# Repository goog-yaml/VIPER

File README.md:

# What is VIPR?

Simply put, VIPR is a open source radio node designed and built around North American mesh communication over LoRa built off of an ESP32-S3 platform. Put less simply, VIPR is another ESP32 development board focused more on frontend, hardware, and size. The project aims to create a small, pocketable radio node that can run independently. Currently the procsessing power of it's latest version (2.0) can only handle small workloads and can only run a Real Time OS in comparison to a fully fledged computer.

**VIPR is currently in Alpha testing, soon to be beta!**

## Current Revision

Currently the board packs a 19mm wide footprint without a screen. The end is equipped with an SMA conector for easy antenna swaps and the side boasts an onboard PCB wifi antenna tied to the ESP32-MINI-1 module.

Future revisions intend to add a screen and interactives to the board to further refine the frontend, all that is needed after that is software and a case!

### Changelog

```
* Redid a proper BOM
    * This included sizing and components selection
* Added back the CH340X
* Reverted to old "pen" form factor
* Created a new "lopsided" board end 
* Added a screen header
* Fixed a regulator issue on the radio portion
* bundled CAD files into production folders <=2.1
```

## Docs

Docs will be coming soon!
<br>

## Versioning system

The project follows a versioning system of major and minor. The first number in the version is the board platform. Whenever the board is fully redone a new major version will be released. Whenever the board has a small tweak to an existing platform version the second number behind the first will be bumped up by one.

A board version of say, 2.1 would indicate platform version 2 with one tweak of the original version 2.0.

#### Latest Journal as of July 28th

For revision 2.1. I introduced a versioning system of major and minor.
 What's new in 2.1?

Mounting holes for M2 screws on the left side of the board and a header connection for a screen. the schematics now include test points for serial, power, and JTAG soon to be onboard for revision 2.2.

Some issues were included in revision 2 that would prevent stable operation of the radio caused by a faulty connection between the regulator for the SX1262 and the inductor managing it.

That's all.

-Matias

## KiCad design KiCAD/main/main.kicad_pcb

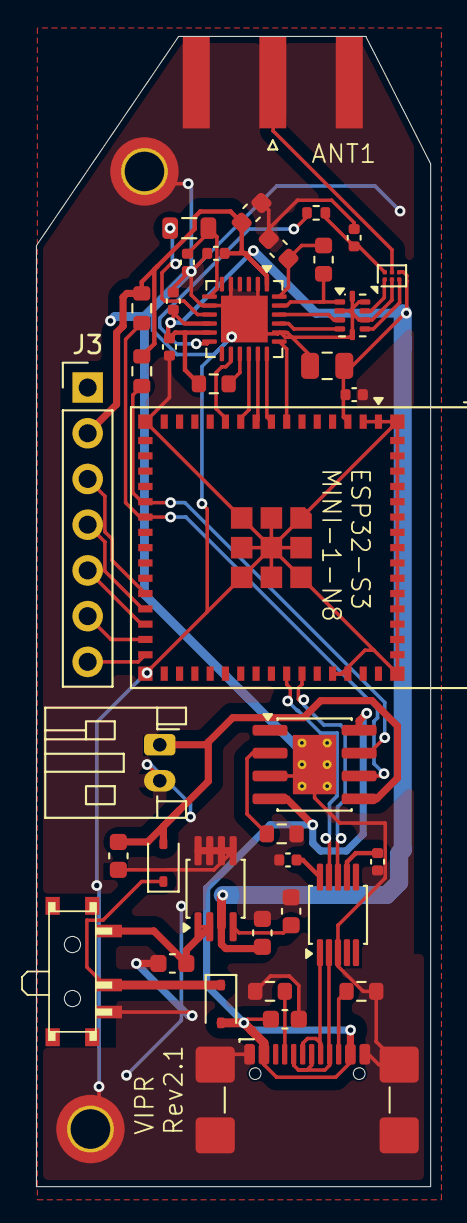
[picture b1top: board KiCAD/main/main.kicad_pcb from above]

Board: 2 copper layers, 21.9 x 63.9 mm, 41 parts (0 on the bottom side), 38 nets.

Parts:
BT1: Battery_Cell; JST_PH_S2B-PH-K_1x02_P2.00mm_Horizontal
C1, C2: 1uF; C_0603_1608Metric
C3: 0.1uf; C_0402_1005Metric
C4: 22uF; C_0805_2012Metric
C5: 470pF; C_0603_1608Metric
C6, C7, C10, C11, C17, C18: 0.1uF; C_0402_1005Metric
C12: 22 pF; C_0603_1608Metric
C13: 100nF; C_0402_1005Metric
C14, C15, C16: 10uF; C_0603_1608Metric
D1, D2: D_Schottky; D_SOD-323
FL1: 0900FM15K0039; Balun_Johanson_0900FM15K0039
H1, H2: MountingHole_Pad; MountingHole_2.2mm_M2_DIN965_Pad_TopBottom
J1: USB_C_Receptacle_USB2.0_14P; USB_C_Receptacle_GCT_USB4110
J2: Conn_Coaxial; SMA_Amphenol_132289_EdgeMount
J3: Conn_01x07_Socket; PinHeader_1x07_P2.54mm_Vertical
L1: 15uH; L_0805_2012Metric
L2: 18 nH; L_0603_1608Metric
R1, R2: 5K1; R_0603_1608Metric
R4, R9, R10: 10K; R_0603_1608Metric
R5: 100R; R_0402_1005Metric
R7: 1.2K; R_0603_1608Metric
SW1: SW_SPDT; SSSS810701
U1: SX1262IMLTRT; QFN-24-1EP_4x4mm_P0.5mm_EP2.6x2.6mm
U2: TP4056-42-ESOP8; SOIC-8-1EP_3.9x4.9mm_P1.27mm_EP2.41x3.3mm_ThermalVias
U3: BGS12P2L; Infineon_PG-TSNP-6-10_0.7x1.1mm_0.7x1.1mm_P0.4mm
U4: ESP32-S3-MINI-1; ESP32-S2-MINI-1
U6: MIC5219-3.3YMM; MSOP-8_3x3mm_P0.65mm
U7: CH340X; MSOP-10_3x3mm_P0.5mm

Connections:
CHRG_BAT: BT1.1 (+), C16.2, D2.2 (A), U2.5 (BAT)
DIO2: R5.1, U1.12 (DIO2)
unnamed: D1.1 (K), D2.1 (K), SW1.2 (B)
unnamed: FL1.3 (RFI_N), U1.22 (RFI_N)
unnamed: FL1.4 (RFI_P), U1.21 (RFI_P)
unnamed: FL1.1 (RFO), L2.2, U1.23 (RFO)
unnamed: FL1.6 (SW_RFI), U3.3 (RF1)
unnamed: FL1.8 (SW_RFO), U3.1 (RF2)
unnamed: J1.A5 (CC1), R1.1
unnamed: J1.B5 (CC2), R2.2
unnamed: J2.1 (In), U3.5 (RFIN)
unnamed: C1.2, SW1.1 (A), U6.1 (EN), U6.2 (IN)
unnamed: L1.2, U1.9 (DCC_SW)
unnamed: C11.2, L1.1, U1.7 (VREG)
unnamed: C12.1, L2.1, U1.24 (VR_PA)
unnamed: R4.2, U1.15 (~RESET)
unnamed: R7.1, U2.2 (PROG)
unnamed: C13.1, R5.2, U3.6 (CTRL)
unnamed: C5.1, U6.4 (BP)
READY: U1.14 (BUSY), U4.11 (IO7)
SCR_CLK: J3.3, U4.26 (IO26)
SCR_CS: J3.7, U4.30 (IO48)
SCR_DC: J3.6, U4.29 (IO34)
SCR_MOSI: J3.4, U4.27 (IO47)
SCR_RES: J3.5, U4.28 (IO33)
SERIAL_N: U4.39 (TXD0), U7.9 (RXD)
SERIAL_P: U4.40 (RXD0), U7.8 (TXD)
SPI_CLK: U1.18 (SCK), U4.8 (IO4)
SPI_CS: U1.19 (NSS), U4.7 (IO3)
SPI_MISO: U1.17 (MOSI), U4.9 (IO5)
SPI_MOSI: U1.16 (MISO), U4.10 (IO6)
USB_DATA+: J1.A6 (D+), J1.B6 (D+), U7.1 (UD+)
USB_DATA-: J1.A7 (D-), J1.B7 (D-), U7.2 (UD-)
V+: C15.1, D1.2 (A), J1.A4 (VBUS), J1.A9 (VBUS), J1.B4 (VBUS), J1.B9 (VBUS), U2.4 (V_{CC}), U2.8 (CE)
V-: BT1.2 (-), C1.1, C2.1, C3.1, C4.1, C5.2, C6.2, C7.2, C10.2, C11.1, C12.2, C13.2, C14.1, C15.2, C16.1, C17.1, C18.1, FL1.2 (GND), FL1.5 (GND), FL1.7 (GND), FL1.9 (GND), FL1.10 (GND), H1.1 (1_1), H2.1 (1_1), J1.A1 (GND), J1.A12 (GND), J1.B1 (GND), J1.B12 (GND), J1.SH (SHIELD), J2.2 (Ext), J3.1, R1.2, R2.1, R7.2, SW1.3 (C), U1.2 (GND), U1.5 (GND), U1.8 (GND), U1.20 (GND), U1.25 (GND), U2.3 (GND), U2.9 (EPAD), U3.2 (GND), U4.1 (GND), U4.2 (GND), U4.42 (GND), U4.43 (GND), U4.46 (GND), U4.47 (GND), U4.48 (GND), U4.49 (GND), U4.50 (GND), U4.51 (GND), U4.52 (GND), U4.53 (GND), U4.54 (GND), U4.55 (GND), U4.56 (GND), U4.57 (GND), U4.58 (GND), U4.59 (GND), U4.60 (GND), U4.61 (GND), U4.62 (GND), U4.63 (GND), U4.64 (GND), U4.65 (GND), U6.5 (GND), U6.6 (GND), U6.7 (GND), U6.8 (GND), U7.3 (GND)
VCC: C2.2, C3.2, C4.2, C6.1, C7.1, C10.1, C14.2, C17.2, C18.2, J3.2, R4.1, R9.2, R10.2, U1.1 (VDD_IN), U1.10 (VBAT), U1.11 (VBAT_IO), U3.4 (VDD), U4.3 (3V3), U6.3 (OUT), U7.7 (VCC), U7.10 (V3)
~CHRG: R10.1, U2.7 (~CHRG), U4.20 (IO16)
~STDBY: R9.1, U2.6 (~STDBY), U4.21 (IO17)

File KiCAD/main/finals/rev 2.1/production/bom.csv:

Designator,Footprint,Quantity,Value,LCSC Part #
BT1,JST_PH_S2B-PH-K_1x02_P2.00mm_Horizontal,1,Battery_Cell,C265094
"C1, C2",0603,2,1uF,C15849
"C10, C11, C17, C18, C3, C6, C7",0402,7,0.1uF,C1525
C12,0603,1,22 pF,C1653
C13,0402,1,100nF,C1525
"C14, C15, C16",0603,3,10uF,C19702
C4,0805,1,22uF,C45783
C5,0603,1,470pF,C1620
"D1, D2",D_SOD-323,2,D_Schottky,C191023
J1,USB_C_Receptacle_GCT_USB4110,1,USB_C_Receptacle_USB2.0_14P,C2765186
J2,SMA_Amphenol_132289_EdgeMount,1,Conn_Coaxial,C3039673
J3,PinHeader_1x07_P2.54mm_Vertical,1,Conn_01x07_Socket,
L1,0805,1,15uH,C383402
L2,0603,1,18 nH,C19721138
"R1, R2",0603,2,5K1,C23186
"R10, R4, R9",0603,3,10K,C25804
R5,0402,1,100R,C25076
R7,0603,1,1.2K,C22765
SW1,SSSS810701,1,SW_SPDT,C97433
U1,QFN-24-1EP_4x4mm_P0.5mm_EP2.6x2.6mm,1,SX1262IMLTRT,C191341
U2,SOIC-8-1EP_3.9x4.9mm_P1.27mm_EP2.41x3.3mm_ThermalVias,1,TP4056-42-ESOP8,C16581
U3,Infineon_PG-TSNP-6-10_0.7x1.1mm_0.7x1.1mm_P0.4mm,1,BGS12P2L,C3312945
U6,MSOP-8_3x3mm_P0.65mm,1,MIC5219-3.3YMM,C628154
U7,MSOP-10_3x3mm_P0.5mm,1,CH340X,C3035748

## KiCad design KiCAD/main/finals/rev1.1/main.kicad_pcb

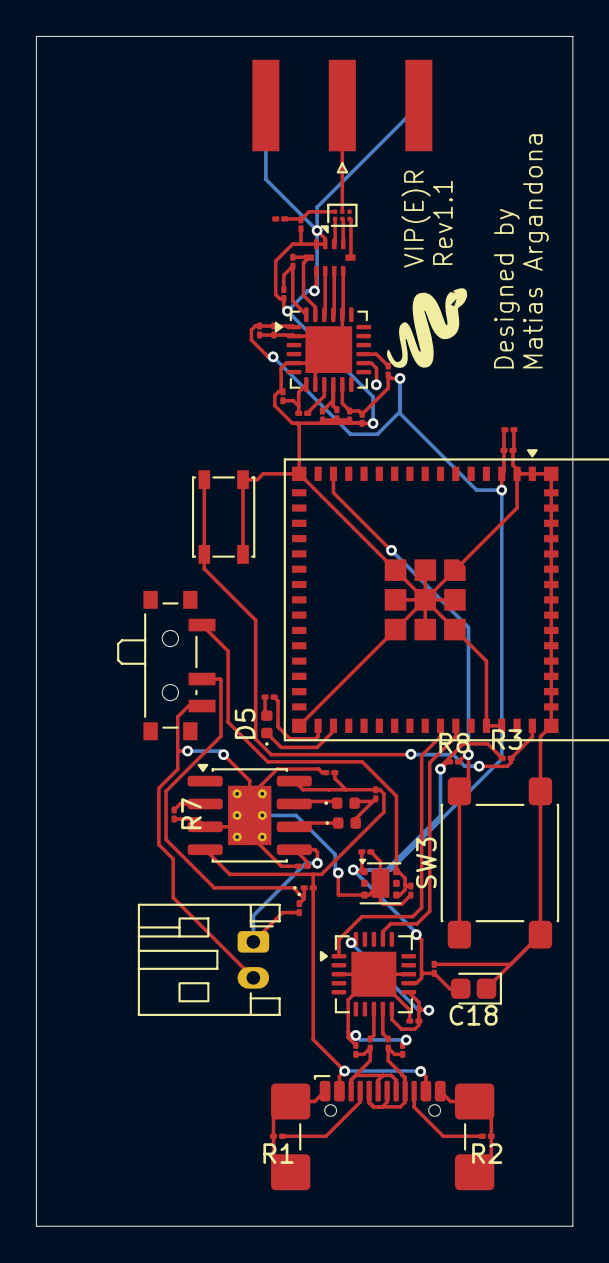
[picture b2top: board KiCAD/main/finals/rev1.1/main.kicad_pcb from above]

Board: 2 copper layers, 29.8 x 66.1 mm, 51 parts (0 on the bottom side), 41 nets.

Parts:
BT1: Battery_Cell; JST_PH_S2B-PH-K_1x02_P2.00mm_Horizontal
C1, C2: 1uF; C_01005_0402Metric
C3: 0.1uf; C_01005_0402Metric
C4: 22uF; C_01005_0402Metric
C5, C8, C15, C16: 10uF; C_01005_0402Metric
C6, C7, C9, C10, C11, C17, C19: 0.1uF; C_01005_0402Metric
C12: 22 pF; C_01005_0402Metric
C13: 100nF; C_01005_0402Metric
C18: 10uF; CP_EIA-1608-08_AVX-J
C20, C21: 47uF; C_01005_0402Metric
D1, D2: D_Schottky; D_01005_0402Metric
D3, D4, D5: LED; LED_0402_1005Metric
FL1: 0900FM15K0039001E; 0900FM15K0039001E_JOT-L
J1: USB_C_Receptacle_USB2.0_14P; USB_C_Receptacle_GCT_USB4110
J2: Conn_Coaxial; SMA_Amphenol_132289_EdgeMount
L1: 15uH; L_01005_0402Metric
L2: 18 nH; L_01005_0402Metric
R1, R2: 5K1; R_01005_0402Metric
R3, R4, R8: 10K; R_01005_0402Metric
R5: 100R; R_01005_0402Metric
R6: 2K; R_01005_0402Metric
R7: 1.2K; R_01005_0402Metric
R9, R10: 27R; R_01005_0402Metric
R12: 1K; R_01005_0402Metric
SW1: SW_SPDT; SW_SPDT_PCM12
SW2: SW_Push; SW_SPST_PTS810
SW3: SW_Push; SW_SPST_PTS645Sx43SMTR92
U1: SX1262IMLTRT; QFN-24-1EP_4x4mm_P0.5mm_EP2.6x2.6mm
U2: TP4056-42-ESOP8; SOIC-8-1EP_3.9x4.9mm_P1.27mm_EP2.41x3.3mm_ThermalVias
U3: TLV75533PDRV; WSON-6-1EP_2x2mm_P0.65mm_EP1x1.6mm
U4: ESP32-S3-MINI-1; ESP32-S2-MINI-1
U5: BGS12WN6E6327; Infineon_PG-TSNP-6-10_0.7x1.1mm_0.7x1.1mm_P0.4mm
U6: FT231XQ; QFN-20-1EP_4x4mm_P0.5mm_EP2.5x2.5mm

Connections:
CHRG: BT1.1 (+), C16.2, D2.2 (A), U2.5 (BAT)
DIO2: R5.1, U1.12 (DIO2)
unnamed: D1.1 (K), D2.1 (K), SW1.2 (B)
unnamed: D3.2 (A), D4.2 (A), R6.2
unnamed: D3.1 (K), U2.6 (~STDBY)
unnamed: D4.1 (K), U2.7 (~CHRG)
unnamed: D5.2 (A), R12.2
unnamed: D5.1 (K), U4.32 (IO36)
unnamed: FL1.3 (RFI_N), U1.22 (RFI_N)
unnamed: FL1.4 (RFI_P), U1.21 (RFI_P)
unnamed: FL1.1 (RFO), L2.2, U1.23 (RFO)
unnamed: FL1.6 (SW_RFI), U5.3 (RF1)
unnamed: FL1.8 (SW_RFO), U5.1 (RF2)
unnamed: J1.A5 (CC1), R1.1
unnamed: J1.B5 (CC2), R2.2
unnamed: J2.1 (In), U5.5 (RFIN)
unnamed: C1.2, SW1.1 (A), U3.4 (EN), U3.6 (IN)
unnamed: L1.2, U1.9 (DCC_SW)
unnamed: C11.2, L1.1, U1.7 (VREG)
unnamed: C12.1, L2.1, U1.24 (VR_PA)
unnamed: R4.2, U1.15 (~RESET)
unnamed: R7.1, U2.2 (PROG)
unnamed: R3.2, SW2.1, U4.45 (EN)
unnamed: R8.2, SW3.1, U4.14 (IO10)
unnamed: R12.1, U4.31 (IO35)
unnamed: C13.1, R5.2, U5.6 (CTRL)
unnamed: C19.2, U6.10 (3V3OUT), U6.11 (~RESET), U6.20 (VCCIO)
unnamed: R9.2, U6.9 (USBDM)
unnamed: R10.1, U6.8 (USBDP)
READY: U1.14 (BUSY), U4.13 (IO9)
SERIAL_N: U4.39 (TXD0), U6.1 (RXD)
SERIAL_P: U4.40 (RXD0), U6.17 (TXD)
SPI_CLK: U1.18 (SCK), U4.10 (IO6)
SPI_CS: U1.19 (NSS), U4.9 (IO5)
SPI_MISO: U1.17 (MOSI), U4.12 (IO8)
SPI_MOSI: U1.16 (MISO), U4.11 (IO7)
USB_DATA+: C21.1, J1.A6 (D+), J1.B6 (D+), R10.2
USB_DATA-: C20.1, J1.A7 (D-), J1.B7 (D-), R9.1
V+: C15.1, D1.2 (A), J1.A4 (VBUS), J1.A9 (VBUS), J1.B4 (VBUS), J1.B9 (VBUS), R6.1, U2.4 (V_{CC}), U2.8 (CE)
V-: BT1.2 (-), C1.1, C2.1, C3.1, C4.1, C5.2, C6.2, C7.2, C8.2, C9.2, C10.2, C11.1, C12.2, C13.2, C15.2, C16.1, C17.1, C18.1, C19.1, C20.2, C21.2, FL1.2 (GND), FL1.5 (GND), FL1.7 (GND), FL1.9 (GND), FL1.10 (GND), J1.A1 (GND), J1.A12 (GND), J1.B1 (GND), J1.B12 (GND), J1.SH (SHIELD), J2.2 (Ext), R1.2, R2.1, R7.2, SW1.3 (C), SW2.2, SW3.2, U1.2 (GND), U1.5 (GND), U1.8 (GND), U1.20 (GND), U1.25 (GND), U2.3 (GND), U2.9 (EPAD), U3.3 (GND), U3.7 (GND), U4.1 (GND), U4.2 (GND), U4.42 (GND), U4.43 (GND), U4.46 (GND), U4.47 (GND), U4.48 (GND), U4.49 (GND), U4.50 (GND), U4.51 (GND), U4.52 (GND), U4.53 (GND), U4.54 (GND), U4.55 (GND), U4.56 (GND), U4.57 (GND), U4.58 (GND), U4.59 (GND), U4.60 (GND), U4.61 (GND), U4.62 (GND), U4.63 (GND), U4.64 (GND), U4.65 (GND), U5.2 (GND), U6.3 (GND), U6.13 (GND), U6.21 (GND)
VCC: C2.2, C3.2, C4.2, C5.1, C6.1, C7.1, C8.1, C9.1, C10.1, C17.2, C18.2, R3.1, R4.1, R8.1, U1.1 (VDD_IN), U1.10 (VBAT), U1.11 (VBAT_IO), U3.1 (OUT), U4.3 (3V3), U5.4 (VDD), U6.12 (VCC)
